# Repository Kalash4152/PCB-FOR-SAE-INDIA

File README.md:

🏎️ Autonomous ATV PCB Designs – SAE India eBaja (DJS Kronos)

Welcome to my repository of PCB designs that I created for the systems of our Autonomous ATV vehicle for the SAE India eBaja competition 🚀. As part of Team DJS Kronos, I worked on designing and developing production-ready PCBs that powered our drive-by-wire systems:

⚙️ SBW (Steer-By-Wire)

🛑 BBW (Brake-By-Wire)

⚡ TVW (Throttle-By-Wire)

🔧 PCB Highlights

✅ One-layer PCB design – optimized for cost & manufacturability

✅ Designed in KiCad 🖥️

✅ Integrated Arduino Mega & ESP32 for control and communication

✅ Onboard Buck Converter for stable power supply ⚡

✅ Proper routing, sizing, and component placement considered for industry-level manufacturing standards 🏭

🏁 Why This Matters

Building an autonomous ATV isn’t just about the mechanical design – the electronics backbone is just as important. These PCBs ensured:

🔹 Reliable communication between control units

🔹 Safe and precise steering, braking, and throttle control

🔹 Robust power regulation even under tough terrain and load conditions

💡 Learning & Impact

This project gave me end-to-end experience in PCB design, from schematics → layout → manufacturable design. It was an exciting challenge to bring core automotive systems into an autonomous format, while balancing performance, reliability, and manufacturability.

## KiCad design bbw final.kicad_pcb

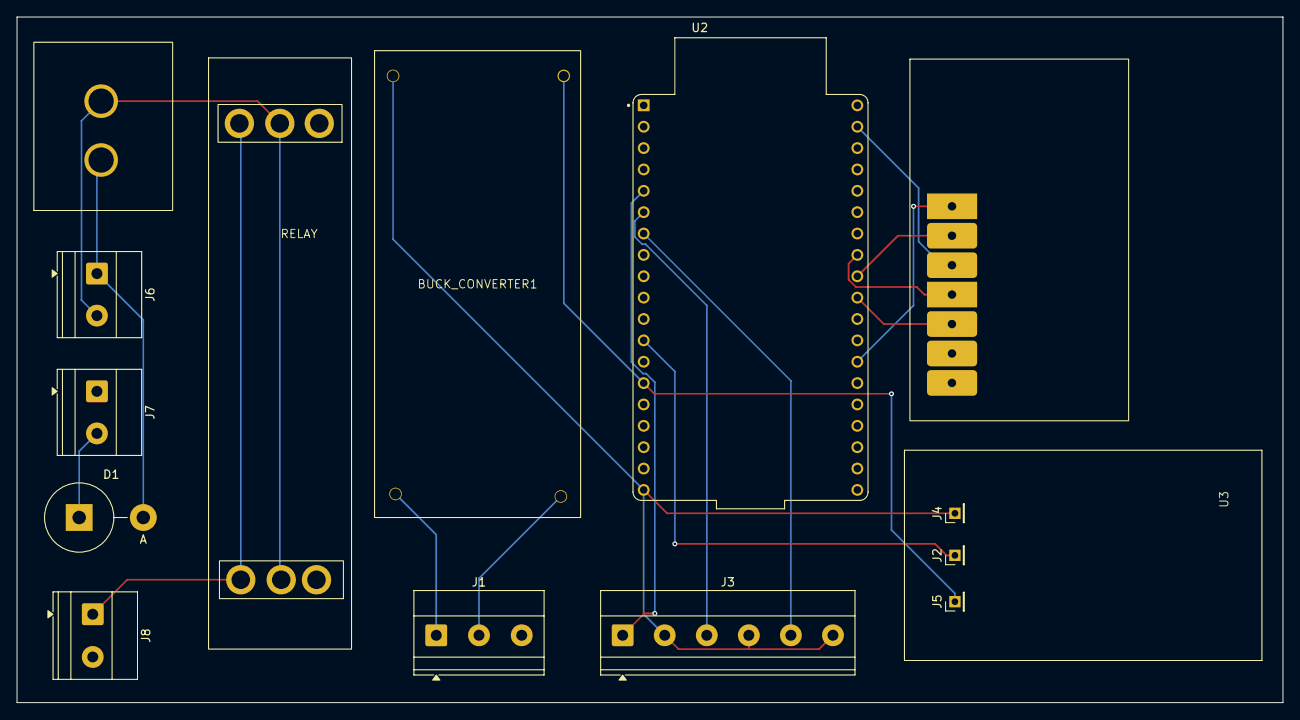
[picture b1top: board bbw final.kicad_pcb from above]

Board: 2 copper layers, 150.5 x 81.5 mm, 14 parts (0 on the bottom side), 17 nets.

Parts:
BUCK_CONVERTER1: Untitled
D1: STPS30L60CW; D_5KPW_P7.62mm_Vertical_AnodeUp
F1: Fuse; FUSEHOLDER
J1: POWER INPUT; TerminalBlock_Phoenix_MKDS-1,5-3-5.08_1x03_P5.08mm_Horizont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
J2, J4, J5: Conn_01x01_Pin; PinHeader_1x01_P2.00mm_Vertical
J3: Conn_01x06_Pin; TerminalBlock_Phoenix_MKDS-1,5-6_1x06_P5.00mm_Horizontal
J6: Conn_01x02_Pin; TerminalBlock_Phoenix_MKDS-1,5-2_1x02_P5.00mm_Horizontal
J7: MOTOR DRIVER +V; TerminalBlock_Phoenix_MKDS-1,5-2_1x02_P5.00mm_Horizontal
J8: +24V; TerminalBlock_Phoenix_MKDS-1,5-2-5.08_1x02_P5.08mm_Horizont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
U1: RELAY
U2: ESP32-DEVKITC-32E; MODULE_ESP32-DEVKITC-32E
U3: mcp esp32

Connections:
+24V: BUCK_CONVERTER1.3 (IN-), J1.1
GND: BUCK_CONVERTER1.4 (IN+), J1.2
unnamed: BUCK_CONVERTER1.1 (OUT+), J3.2, J3.4, J3.6, J4.1, U2.J2_19 (EXT_5V)
unnamed: BUCK_CONVERTER1.2 (OUT-), J5.1, U2.J2_14 (GND_J2_14)
unnamed: D1.2 (A), F1.2, J6.1
unnamed: D1.1 (K), J7.2
unnamed: J2.1, U2.J2_12 (IO14)
unnamed: J3.1, U2.J2_5 (IO34)
unnamed: J3.3, U2.J2_6 (IO35)
unnamed: J3.5, U2.J2_7 (IO32)
unnamed: F1.1, J6.2, U1.2 (B)
unnamed: J8.1, U1.1 (A)
unnamed: U2.J3_13 (IO4), U3.9 (INT)
unnamed: U2.J3_10 (IO5), U3.5 (CS)
unnamed: U2.J3_9 (IO18), U3.6 (SCLK)
unnamed: U2.J3_8 (IO19), U3.4 (MISO)
unnamed: U2.J3_2 (IO23), U3.1 (MOSI)

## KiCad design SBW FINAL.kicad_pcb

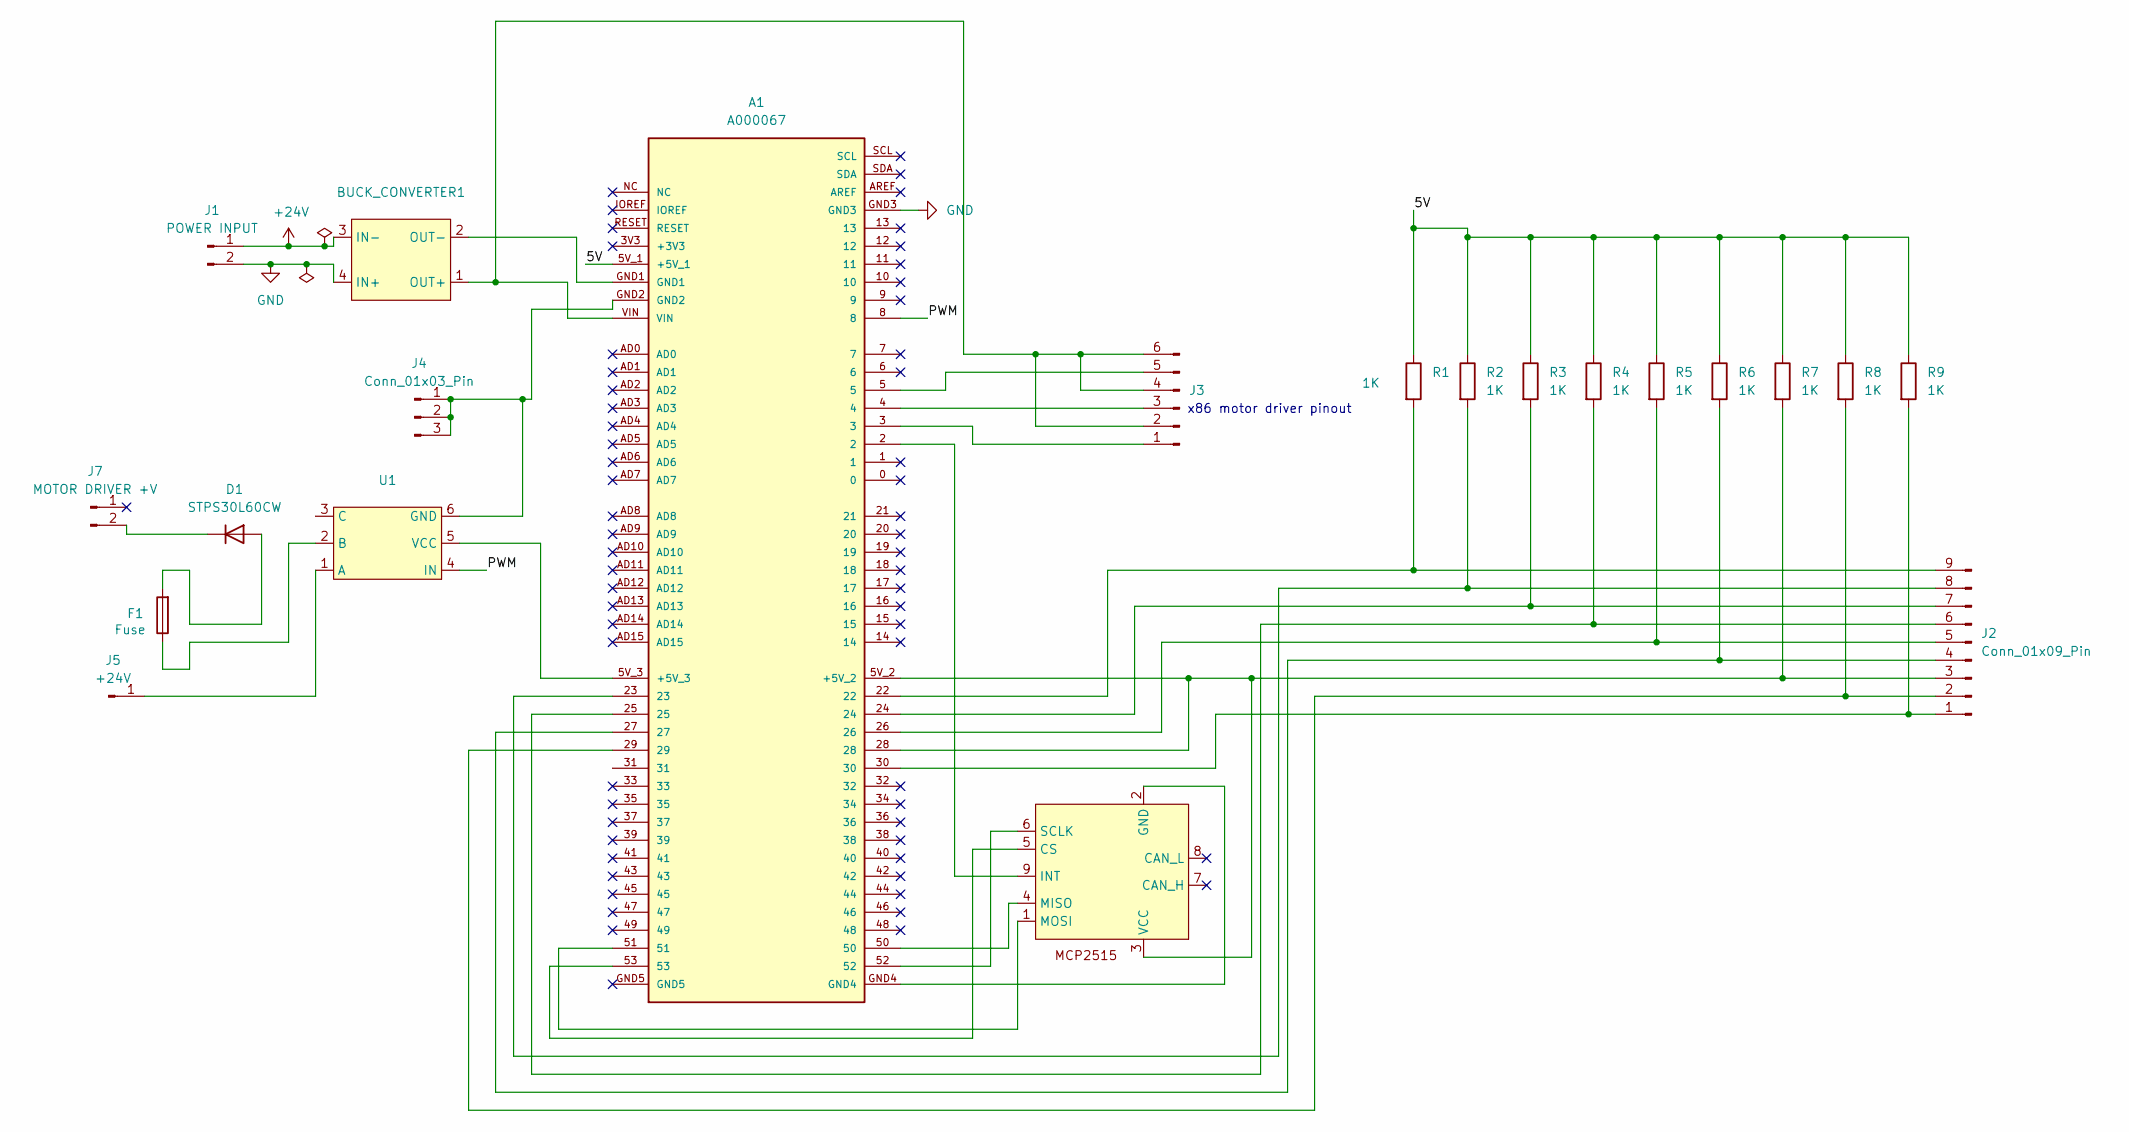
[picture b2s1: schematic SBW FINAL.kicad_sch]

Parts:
A1: A000067; MODULE_A000067; PARTREV 3
BUCK_CONVERTER1: Untitled
D1: STPS30L60CW; D_5KPW_P7.62mm_Vertical_AnodeUp
F1: Fuse; FUSEHOLDER
J1: POWER INPUT; TerminalBlock_Phoenix_MKDS-1,5-2-5.08_1x02_P5.08mm_Horizont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
J2: Conn_01x09_Pin; TerminalBlock_Phoenix_MKDS-1,5-9_1x09_P5.00mm_Horizontal
J3: Conn_01x06_Pin; TerminalBlock_Phoenix_MKDS-1,5-6_1x06_P5.00mm_Horizontal
J4: Conn_01x03_Pin; TerminalBlock_Phoenix_MKDS-1,5-3_1x03_P5.00mm_Horizontal
J5: +24V; TerminalBlock_Phoenix_MKDS-1,5-2-5.08_1x02_P5.08mm_Horizont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
J7: MOTOR DRIVER +V; TerminalBlock_Phoenix_MKDS-1,5-2_1x02_P5.00mm_Horizontal
R1, R2, R3, R4, R5, R6, R7, R8, R9: 1K; R_Axial_DIN0204_L3.6mm_D1.6mm_P1.90mm_Vertical
U1: Untitled
U3: MCP2515

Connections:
+24V: BUCK_CONVERTER1.3 (IN-), J1.1
/5V: A1.5V_1 (+5V_1), R1.1, R2.1, R3.1, R4.1, R5.1, R6.1, R7.1, R8.1, R9.1
/PWM: A1.8, U1.4 (IN)
GND: A1.GND3, BUCK_CONVERTER1.4 (IN+), J1.2
unnamed: A1.5V_2 (+5V_2), A1.28, J2.3, R7.2, U3.3 (VCC)
unnamed: A1.5V_3 (+5V_3), U1.5 (VCC)
unnamed: A1.VIN, BUCK_CONVERTER1.1 (OUT+), J3.2, J3.4, J3.6
unnamed: A1.GND1, BUCK_CONVERTER1.2 (OUT-)
unnamed: D1.2 (A), F1.2
unnamed: D1.1 (K), J7.2
unnamed: A1.30, J2.1, R9.2
unnamed: A1.29, J2.2, R8.2
unnamed: A1.27, J2.4, R6.2
unnamed: A1.26, J2.5, R5.2
unnamed: A1.25, J2.6, R4.2
unnamed: A1.24, J2.7, R3.2
unnamed: A1.23, J2.8, R2.2
unnamed: A1.22, J2.9, R1.2
unnamed: A1.3, J3.1
unnamed: A1.4, J3.3
unnamed: A1.5, J3.5
unnamed: A1.GND2, J4.1, J4.2, J4.3, U1.6 (GND)
unnamed: J5.1, U1.1 (A)
unnamed: F1.1, U1.2 (B)
unnamed: A1.53, U3.5 (CS)
unnamed: A1.GND4, U3.2 (GND)
unnamed: A1.2, U3.9 (INT)
unnamed: A1.50, U3.4 (MISO)
unnamed: A1.51, U3.1 (MOSI)
unnamed: A1.52, U3.6 (SCLK)

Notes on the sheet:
x86 motor driver pinout

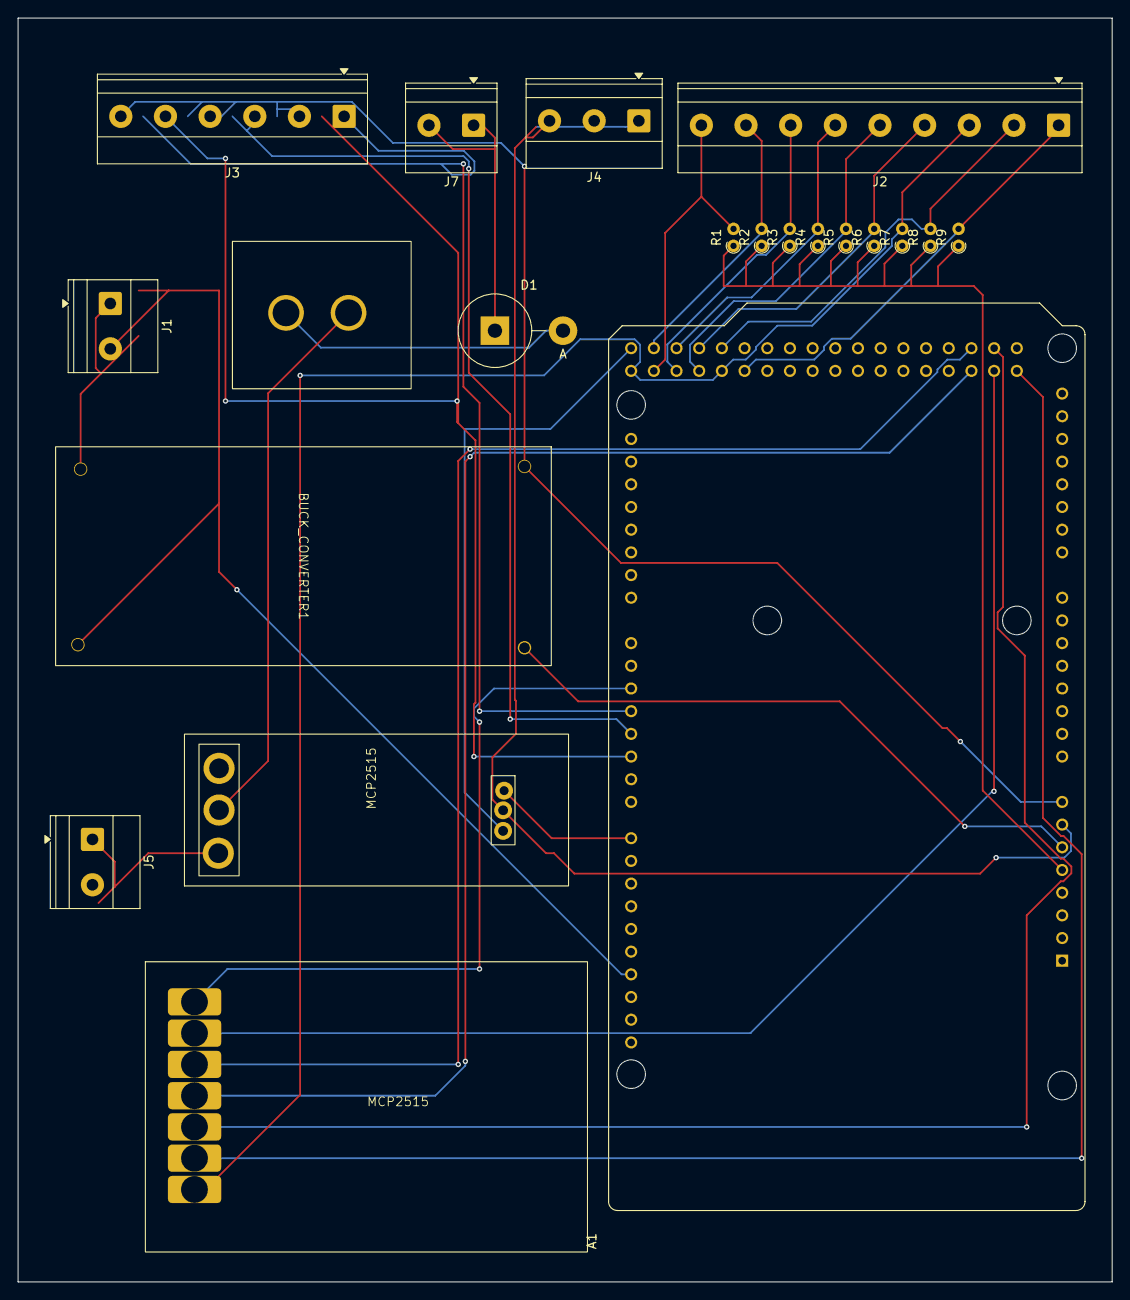
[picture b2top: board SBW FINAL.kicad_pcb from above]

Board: 2 copper layers, 122.5 x 141.5 mm, 21 parts (0 on the bottom side), 30 nets.

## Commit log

2025-08-30 Add files via upload
    🏎️ Autonomous ATV PCB Designs – SAE India eBaja (DJS Kronos)
    Welcome to my repository of PCB designs that I created for the systems of our Autonomous ATV vehicle for the SAE India eBaja competition 🚀. As part of Team DJS Kronos, I worked on designing and devel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
    ⚙️ SBW (Steer-By-Wire)
    🛑 BBW (Brake-By-Wire)
    ⚡ TVW (Throttle-By-Wire)
    🔧 PCB Highlights
